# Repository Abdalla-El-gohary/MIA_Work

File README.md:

# MIA_Work
[resources](https://circuitdigest.com/microcontroller-projects/interfacing-color-sensor-with-arduino)

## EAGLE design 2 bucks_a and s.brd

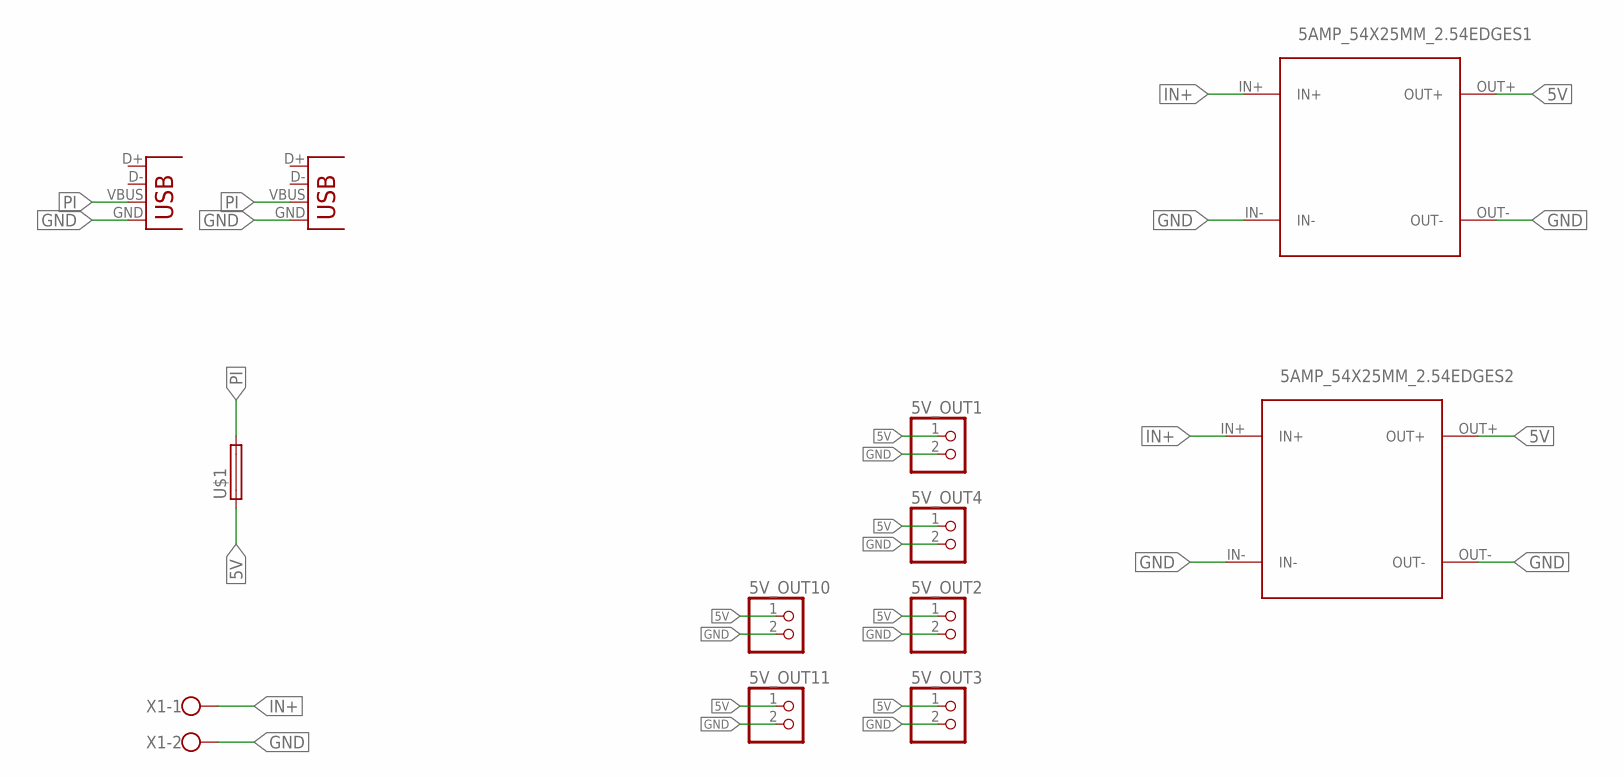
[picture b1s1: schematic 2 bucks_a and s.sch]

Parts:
5AMP_54X25MM_2.54EDGES1, 5AMP_54X25MM_2.54EDGES2: BUCKCONVERTER_5AMP_54X25MM
5V_OUT1, 5V_OUT2, 5V_OUT3, 5V_OUT4, 5V_OUT10, 5V_OUT11: PINHD-2_DATA; 1X02_DATA
U$1: FUSE_HOLDER; SH22,5A
X1: ROSTA.POWER; W239-302
X2, X4: USB-A-H

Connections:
5V: 5AMP_54X25MM_2.54EDGES1.OUT+, 5AMP_54X25MM_2.54EDGES2.OUT+, 5V_OUT1.1, 5V_OUT2.1, 5V_OUT3.1, 5V_OUT4.1, 5V_OUT10.1, 5V_OUT11.1, U$1.1
GND: 5AMP_54X25MM_2.54EDGES1.IN-, 5AMP_54X25MM_2.54EDGES1.OUT-, 5AMP_54X25MM_2.54EDGES2.IN-, 5AMP_54X25MM_2.54EDGES2.OUT-, 5V_OUT1.2, 5V_OUT2.2, 5V_OUT3.2, 5V_OUT4.2, 5V_OUT10.2, 5V_OUT11.2, X1.2, X2.GND, X4.GND
IN+: 5AMP_54X25MM_2.54EDGES1.IN+, 5AMP_54X25MM_2.54EDGES2.IN+, X1.1
PI: U$1.2, X2.VBUS, X4.VBUS

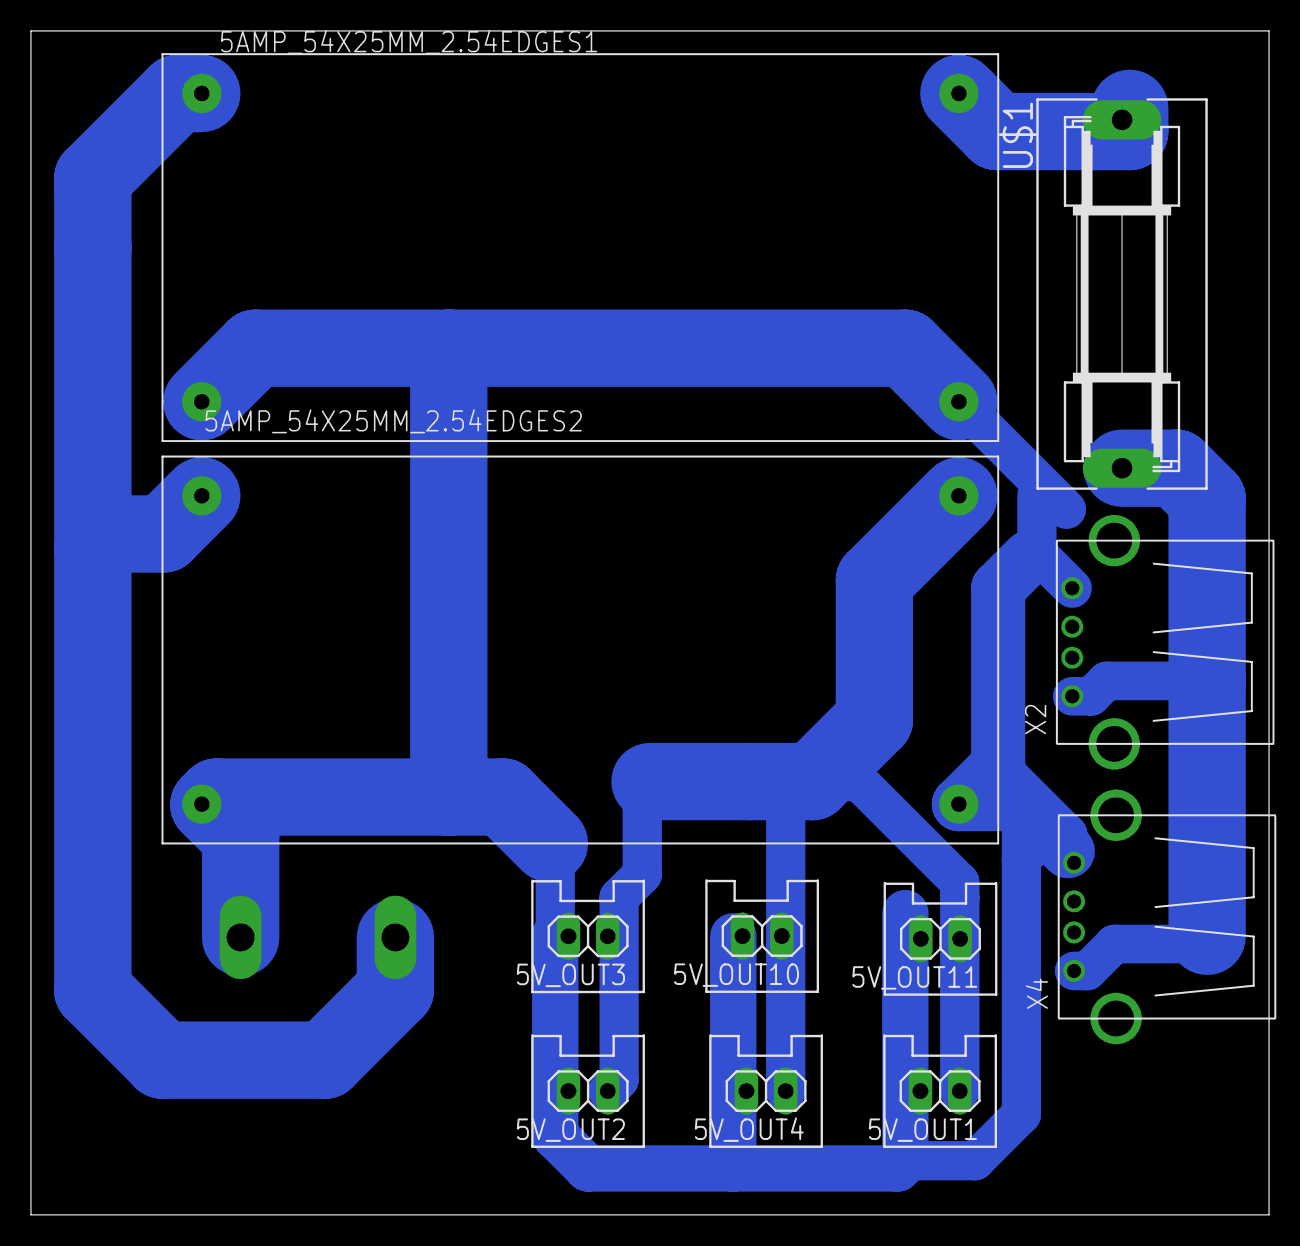
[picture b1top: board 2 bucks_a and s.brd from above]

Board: 2 copper layers, 80.0 x 76.5 mm, 12 parts (1 on the bottom side), 4 nets.

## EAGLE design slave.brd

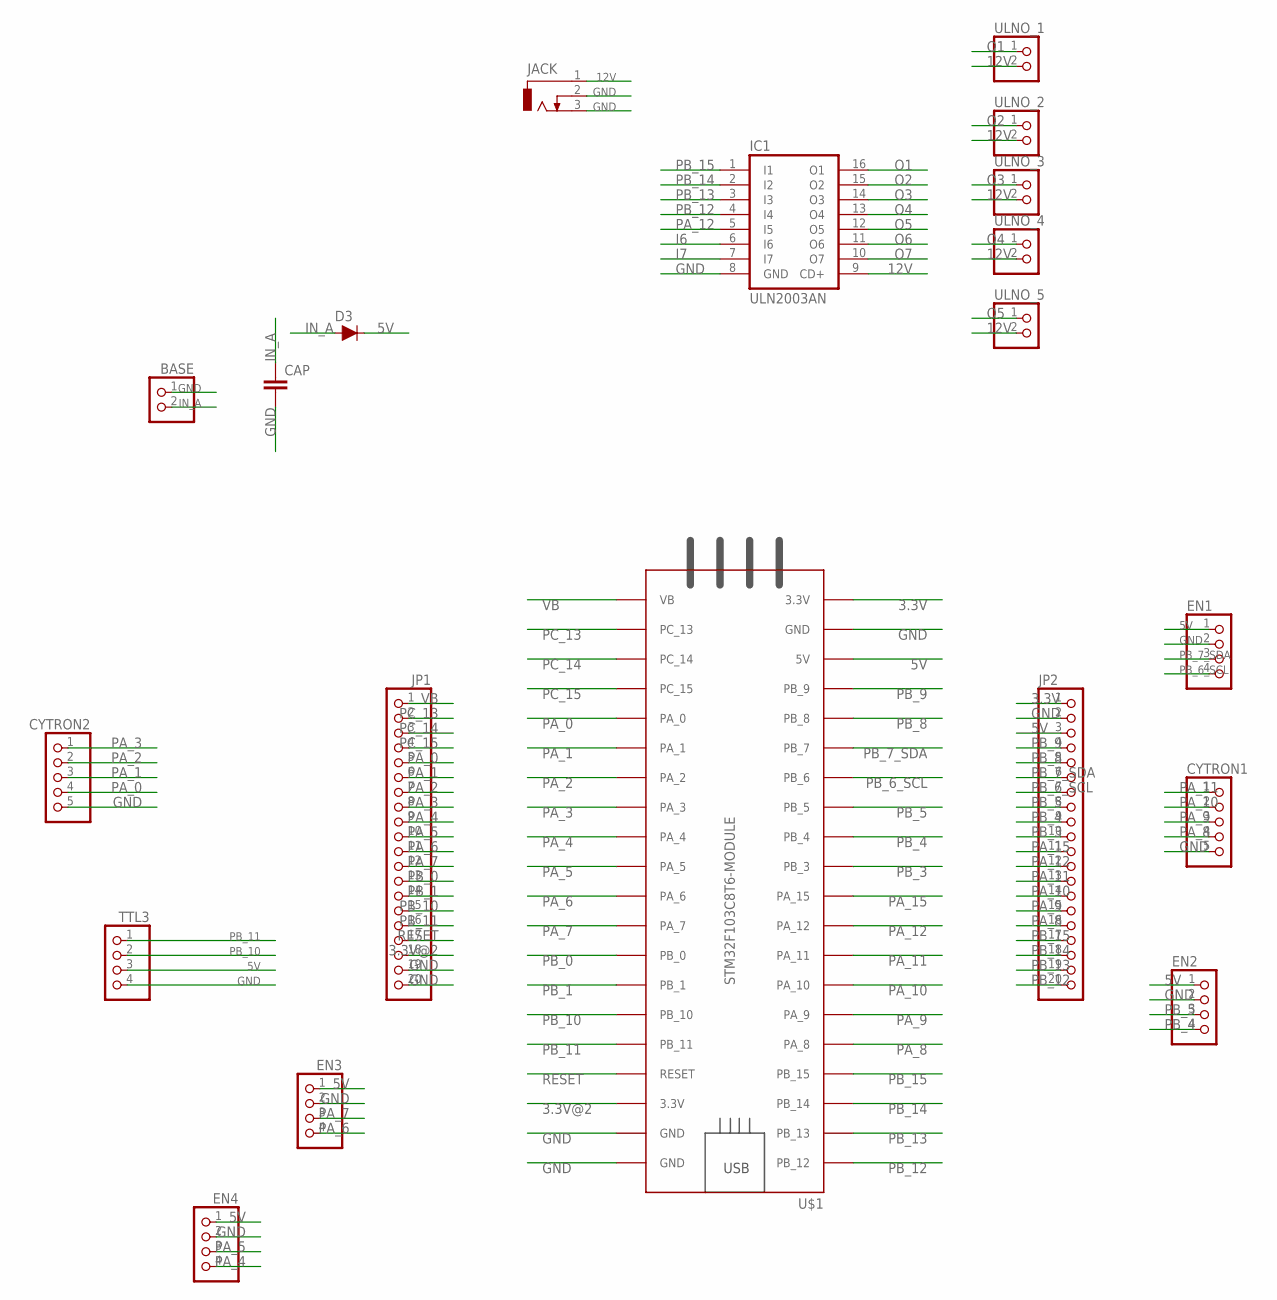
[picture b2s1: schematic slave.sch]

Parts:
BASE: PINHD-2_DATA; 1X02_DATA
CAP: CAPACITOR; C025-025X050
CYTRON1, CYTRON2: PINHD-5_DATA; 1X05_DATA
D3: 200mA/100V/1V; DIODE-1N4148
EN1, EN2, EN3, EN4: PINHD-4_DATA; 1X04_DATA
IC1: ULN2003AN; DIL16
JACK: CON_JACK; DCJ0303
JP1, JP2: PINHD-1X20; 1X20
TTL3: PINHD-4_DATA; 1X04_DATA
U$1: STM32F103C8T6-MODULE
ULNO_1, ULNO_2, ULNO_3, ULNO_4, ULNO_5: PINHD-2_DATA; 1X02_DATA

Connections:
3.3V: JP2.1, U$1.3.3V_1 (3.3V)
3.3V@2: JP1.18, U$1.3.3V_2 (3.3V)
5V: D3.C, EN1.1, EN2.1, EN3.1, EN4.1, JP2.3, TTL3.3, U$1.5V
12V: IC1.9 (CD+), JACK.1, ULNO_1.2, ULNO_2.2, ULNO_3.2, ULNO_4.2, ULNO_5.2
GND: BASE.1, CAP.2, CYTRON1.5, CYTRON2.5, EN1.2, EN2.2, EN3.2, EN4.2, IC1.8 (GND), JACK.2, JACK.3, JP1.19, JP1.20, JP2.2, TTL3.4, U$1.GND_1 (GND), U$1.GND_2 (GND), U$1.GND_3 (GND)
I6: IC1.6 (I6)
I7: IC1.7 (I7)
IN_A: BASE.2, CAP.1, D3.A
O1: IC1.16 (O1), ULNO_1.1
O2: IC1.15 (O2), ULNO_2.1
O3: IC1.14 (O3), ULNO_3.1
O4: IC1.13 (O4), ULNO_4.1
O5: IC1.12 (O5), ULNO_5.1
O6: IC1.11 (O6)
O7: IC1.10 (O7)
PA_0: CYTRON2.4, JP1.5, U$1.PA_0
PA_1: CYTRON2.3, JP1.6, U$1.PA_1
PA_2: CYTRON2.2, JP1.7, U$1.PA_2
PA_3: CYTRON2.1, JP1.8, U$1.PA_3
PA_4: EN4.4, JP1.9, U$1.PA_4
PA_5: EN4.3, JP1.10, U$1.PA_5
PA_6: EN3.4, JP1.11, U$1.PA_6
PA_7: EN3.3, JP1.12, U$1.PA_7
PA_8: CYTRON1.4, JP2.16, U$1.PA_8
PA_9: CYTRON1.3, JP2.15, U$1.PA_9
PA_10: CYTRON1.2, JP2.14, U$1.PA_10
PA_11: CYTRON1.1, JP2.13, U$1.PA_11
PA_12: IC1.5 (I5), JP2.12, U$1.PA_12
PA_15: JP2.11, U$1.PA_15
PB_0: JP1.13, U$1.PB_0
PB_1: JP1.14, U$1.PB_1
PB_3: JP2.10, U$1.PB_3
PB_4: EN2.4, JP2.9, U$1.PB_4
PB_5: EN2.3, JP2.8, U$1.PB_5
PB_6_SCL: EN1.4, JP2.7, U$1.PB_6
PB_7_SDA: EN1.3, JP2.6, U$1.PB_7
PB_8: JP2.5, U$1.PB_8
PB_9: JP2.4, U$1.PB_9
PB_10: JP1.15, TTL3.2, U$1.PB_10
PB_11: JP1.16, TTL3.1, U$1.PB_11
PB_12: IC1.4 (I4), JP2.20, U$1.PB_12
PB_13: IC1.3 (I3), JP2.19, U$1.PB_13
PB_14: IC1.2 (I2), JP2.18, U$1.PB_14
PB_15: IC1.1 (I1), JP2.17, U$1.PB_15
PC_13: JP1.2, U$1.PC_13
PC_14: JP1.3, U$1.PC_14
PC_15: JP1.4, U$1.PC_15
RESET: JP1.17, U$1.RESET
VB: JP1.1, U$1.VB

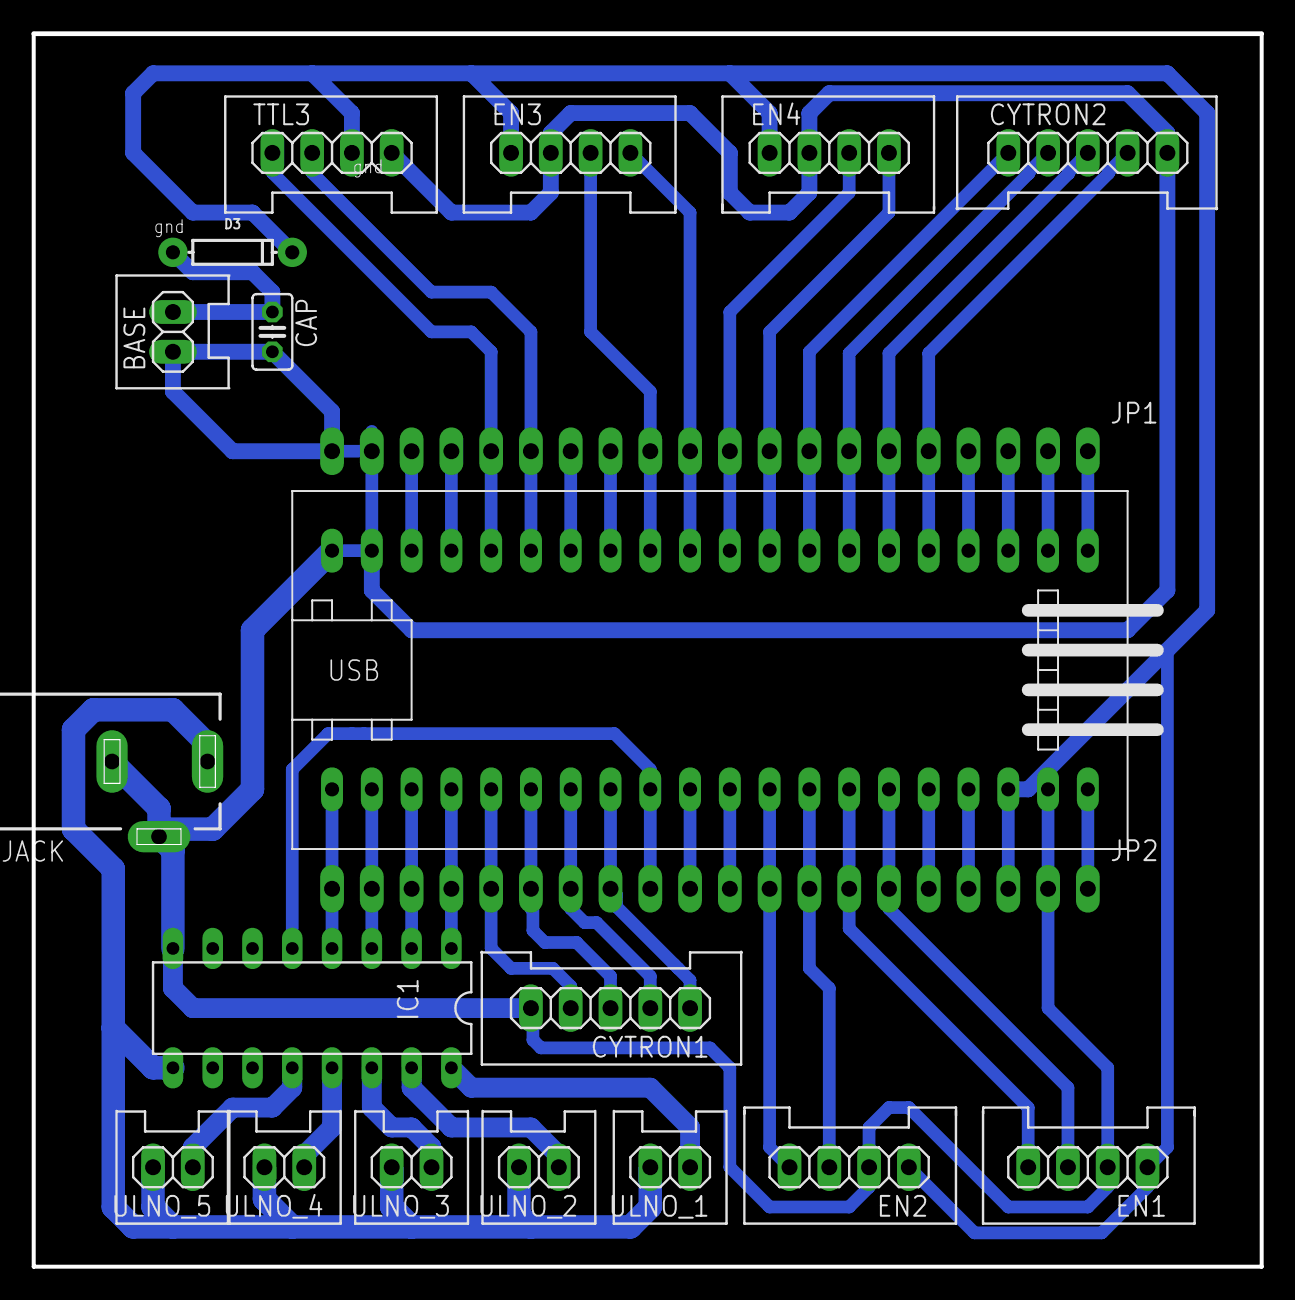
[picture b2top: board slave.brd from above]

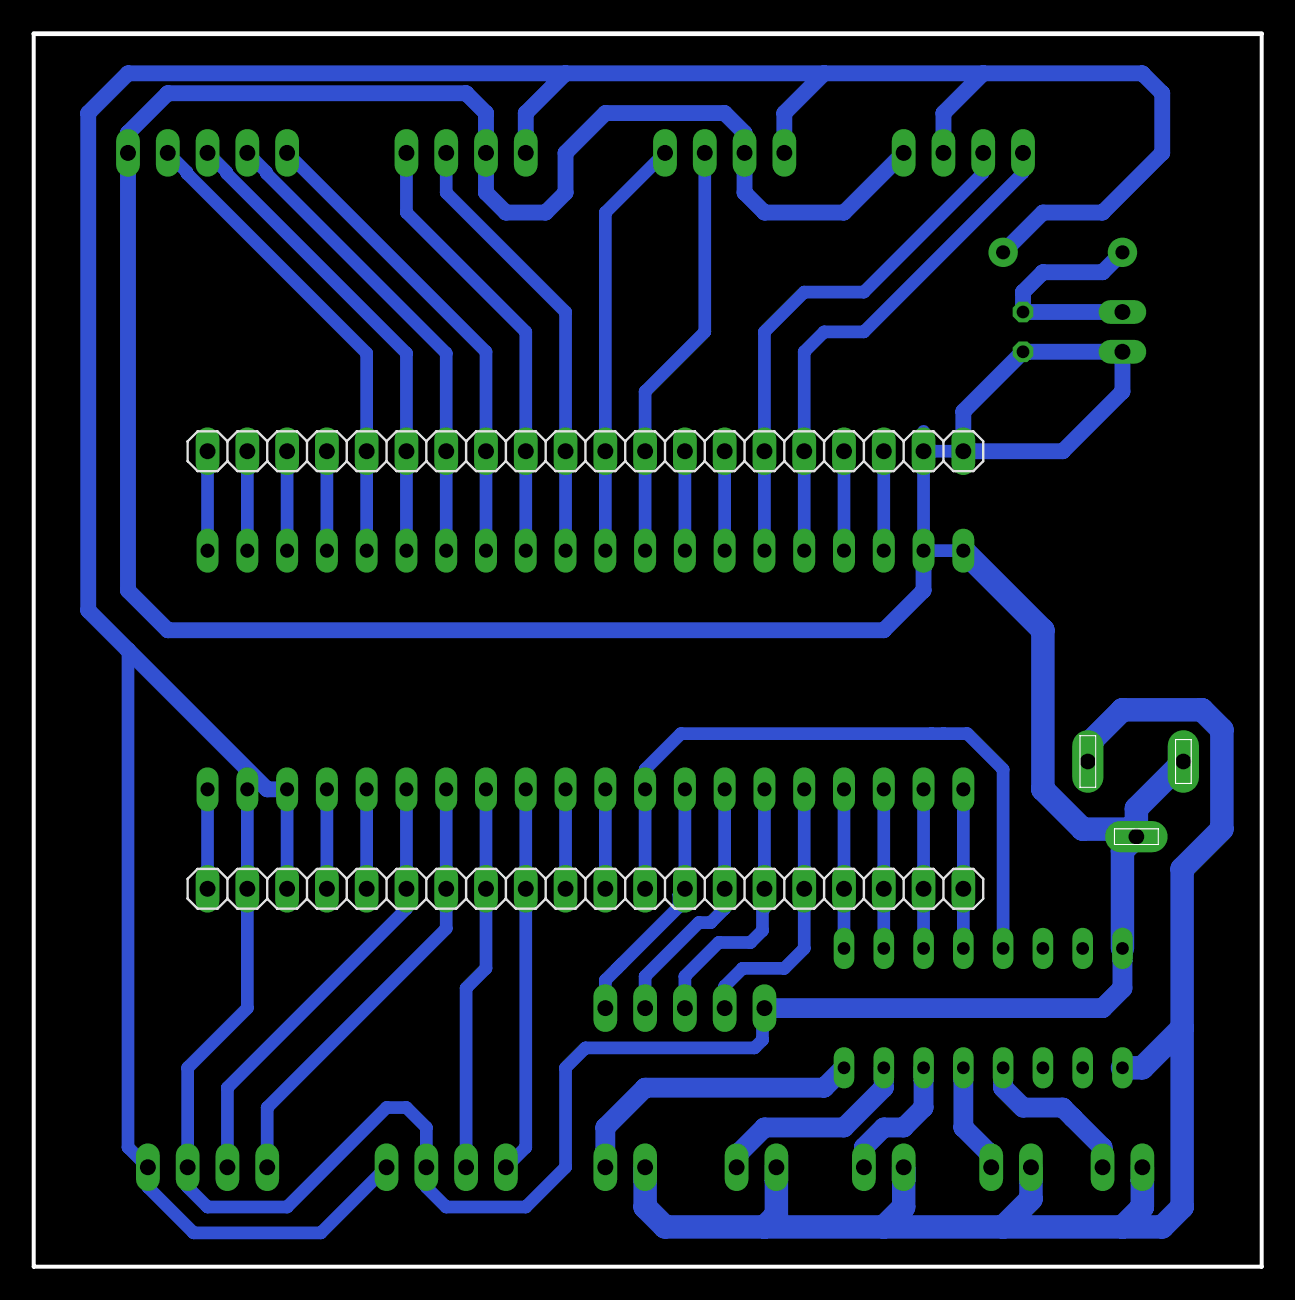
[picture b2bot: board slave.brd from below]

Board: 2 copper layers, 78.4 x 78.7 mm, 20 parts (2 on the bottom side), 45 nets.

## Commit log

2023-02-15 buck
2023-09-05 switches
2024-03-21 color-sensor
